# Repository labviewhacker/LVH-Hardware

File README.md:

hardware
========

Hardware Designs

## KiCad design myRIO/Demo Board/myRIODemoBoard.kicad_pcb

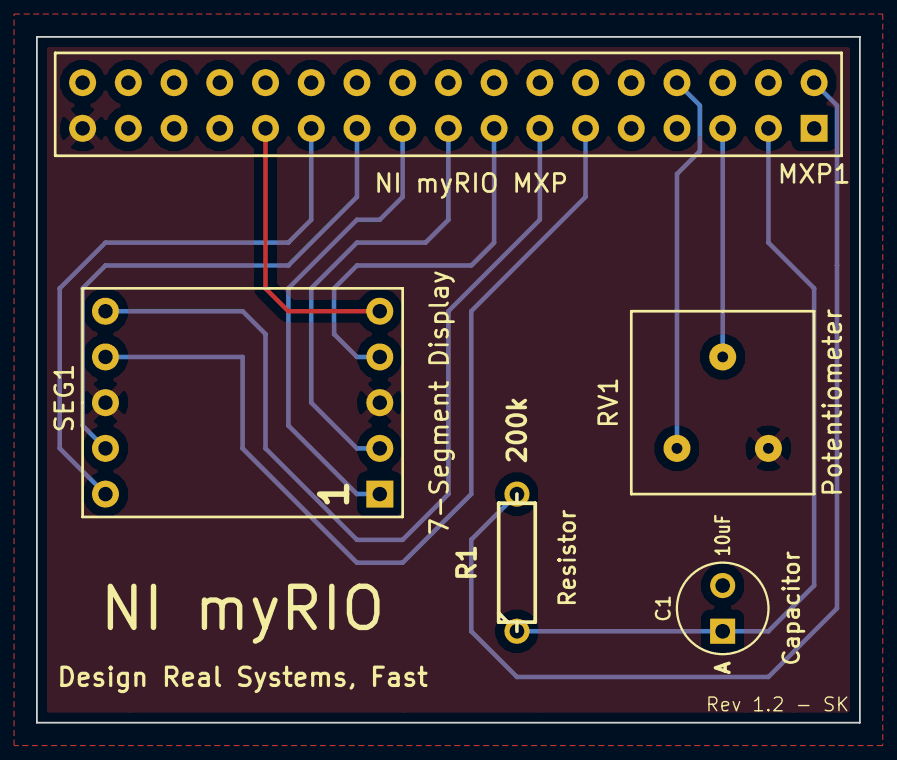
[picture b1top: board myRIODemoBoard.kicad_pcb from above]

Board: 2 copper layers, 45.7 x 38.1 mm, 5 parts (0 on the bottom side), 13 nets.

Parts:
C1: 10uF; C1V5
MXP1: NI myRIO MXP; MXP
R1: 200k; R3
RV1: Potentiometer; POT_3386F
SEG1: 7-Segment Display; LTS-5501AB

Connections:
+3.3V: MXP1.33, RV1.3, SEG1.3, SEG1.8
GND: C1.2, MXP1.6, MXP1.8, MXP1.12, MXP1.16, MXP1.20, MXP1.24, MXP1.28, MXP1.30, RV1.1
unnamed: C1.1, MXP1.3, R1.1
unnamed: MXP1.2, R1.2
unnamed: MXP1.5, RV1.2
a: MXP1.11, SEG1.7
b: MXP1.13, SEG1.6
c: MXP1.15, SEG1.4
d: MXP1.17, SEG1.2
dp: MXP1.25, SEG1.5
e: MXP1.19, SEG1.1
f: MXP1.21, SEG1.9
g: MXP1.23, SEG1.10

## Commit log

2014-02-21 Added basic myRIO demo board schematic.
2014-02-21 Complete PCB. Needs Review.
2014-02-24 Small updates to footprints, schematic, etc.
2014-02-25 Prototype Order of Rev 1.0
2014-03-03 Added BOM
2014-03-03 Updated myRIO Demo Board to Rev 1.1. Modified component IDs for manufacturing. Adjusted silk screen.
2014-03-03 Regenerated Gerbers
2014-03-03 Updated BOM and component IDs to work better with Screaming Circuits parser
2014-03-06 Reorganized hierarchy. Added Standard Adapter Layout - To be used as a template for myRIO boards.
2014-03-10 Merged components from RPI project.
2014-04-07 Updated R1 to 200k in schematic, BOM and silkscreen Generated new gerbers.
2014-04-07 Updated Gerbers.
2014-04-07 Reved to 1.2
